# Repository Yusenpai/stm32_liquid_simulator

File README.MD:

# Giả lập chất lỏng trên STM32U585

Đây là một mạch in nhỏ do mình thiết kế với vi điều khiển STM32U585CIU6, chạy giả lập chất lỏng, hiển thị chất lỏng lên màn hình LED đơn; có thể tương tác với người dùng bằng cách nghiêng, lắc. Ý tưởng dựa trên project của mixela (YT: [Fluid Simulation Pedant](https://www.youtube.com/watch?v=jis1MC5Tm8k&t=2007s))

## Cài đặt

Sử dụng STM32CubeIDE import project dưới dạng CMake, hoặc sử dụng VSCode kết hợp STM32 VSCode Extension và Cmake Tools. Build với cấu hình Release. File elf sau khi build nằm ở build/Release/.

## Phần mềm

### Hiển thị

Màn hình gồm 216 LED, tạo thành từ ma trận LED 16x16, với 4 góc bị khuyết để tạo thành hình tròn. LED được điều khiển trực tiếp bằng chân GPIO của vi điều khiển. Ma trận LED được nối với kỹ thuật Charlieplexing:

Ưu điểm:

- Số lượng chân GPIO dùng để điều khiển màn hình LED là tối thiểu
- Tận dụng tốc độ bật tắt cao của chân GPIO vi điều khiển, tối đa 80MHz (nguồn :datasheet). Không cần dùng IC ngoài.
- Đơn giản hoá vẽ mạch in: Số lượng via sử dụng ít, cho phép đặt linh kiện ngay dưới màn hình LED. Bạn có thể xem phần giải thích ở video của mixela ().
- Độ sáng đồng nhất, do tại một thời điểm chỉ có một LED sáng.

Nhược điểm:

- Khó hiểu, khó sử dụng: ứng dụng tính chất 3 trạng thái của chân GPIO để điều khiển LED, dẫn đến khó sử dụng hơn những phương pháp điều khiển LED khác.
- Phần mềm phức tạp: Cần phải điều khiển GPIO với tốc độ rất cao, tiêu tốn nhiều tài nguyên CPU. Tại một thời điểm chỉ điều khiển được 1 LED sáng/tắt nên tốc độ quét trên LED phải rất cao.

### Điều khiển màn hình LED với STM32U585

- Có tất cả 216 LED. Do giới hạn của charlieplexing nên chỉ điều khiển sáng/tắt được 1 LED theo ý muốn. Trong một khoảng thời gian nhỏ (1ms), chia thành 216 phần thời gian bằng nhau, mỗi phần thời gian dành cho 1 LED. Do mắt lưu ảnh (nguồn -) nên mắt sẽ nhìn thấy toàn bộ bức ảnh do 216 LED tạo thành. Một khung ảnh (tạo thành từ 216 LED) cần 1ms để hiển thị. Vậy tốc độ làm mới (FPS) là 1000Hz.
- Điều khiển 1 LED sáng tắt bằng cách ghi vào hai thanh ghi ODR và MODER của GPIOA. ODR điều khiển mức điện áp (0/1). MODER điều khiển chế độ là ngõ ra hay ngõ vào (trở kháng cao).
- Mỗi LED sáng tương ứng với một giá trị của ODR và một giá trị MODER. Tất cả giá trị này được tính sẵn cho 216 LED và lưu vào một mảng. Khi cần sáng LED nào thì lấy giá trị tương ứng từ mảng này, lưu vào một mảng tạm. Led không sáng thì ODR = 0 và MODER = 0.
- Mảng tạm chứa tất cả các LED cần sáng để tạo thành ảnh. GPDMA thay thế cho CPU di chuyển dữ liệu từ mảng này sang hai thanh ghi GPIOA->ODR và GPIOA->MODER với tốc độ cao. Với mỗi LED GPDMA sử dụng hai kênh, một kênh để ghi vào ODR, một kênh ghi vào MODER. Hai kênh tuy độc lập lẫn nhau, như đều được trigger bởi một TIMER. Khi trigger xảy ra, cả hai thanh ghi ODR và MODER gần như được ghi cùng lúc, giúp giảm hiện tượng nhiễu màn hình. Kết hợp với chế độ circular mode và 2D addressing, GPDMA tự động chuyển sang LED tiếp theo cần sáng rồi chờ trigger từ timer; khi tới phần tử cuối trong mảng tạm, GPDMA tự động quay vòng địa chỉ về phần tử đầu tiên.
- TIMER15 được cấu hình đếm lên và reset mỗi 1/216 ms. Tín hiệu trigger gửi tới GPDMA điều khiển hoạt động của nó.
  
### Mô phỏng chất lỏng

- CPU của STM32U585 dành 100% thời gian để chạy mô phỏng chất lỏng. Phần mềm mô phỏng chất lỏng sử dụng phương pháp FLIP (Fluid Implicit Particle). Tham khảo tại [đây](https://www.sciencedirect.com/science/article/abs/pii/0010465588900203)
- Phần mềm được port sang C để tương thích với vi điều khiển. Phần mềm chưa hoàn toàn tối ưu. Nếu bạn muốn tự viết một cái, tham khảo kênh YT [Ten Minute Physics](https://www.youtube.com/@TenMinutePhysics/videos).
- MPU6050 là cảm biến dùng để đo hướng và độ lớn của gia tốc trọng trường. Giá trị này được truyền vào hàm mô phỏng chất lỏng. Giao tiếp I2C với MPU6050 ở chế độ non-block sử dụng DMA hoặc ngắt.
- CPU chạy ở tần số 160MHz. CPU chạy hàm mô phỏng mỗi 1/60 cho tốc độ cập nhật khung hình là 60 FPS.

### Chế độ tiết kiệm điện

- Khi không tương tác với người dùng (để yên một chỗ) lâu hơn 5s, vi điều khiển sẽ đi ngủ. Khi lắc mạnh sẽ tỉnh dậy. MPU6050 có lõi xử lý bên trong có khả năng gọi MCU tỉnh dậy khi phát hiện gia tốc lớn. Cái này là ý tưởng thôi chứ mình lười nên chưa làm.
- Mạch xài pin LIR2450 là loại pin đồng xu sạc lại được. Tuy nhiên nó có dung lượng nhỏ (khoảng 50mAh). Sử dụng liên tục trong khoảng 1h là hết pin.

## Phần cứng

- Mạch in hình tròn bán kính 1.5cm. Vừa đủ lớn để nhét vừa màn hình 16x16 LED (mỗi LED 0402).
- Do màn hình LED phải dùng rất nhiều Via nên đặt linh kiện ở mặt sau rất khó. May là charlieplexing có biến thể sử dụng ít via hơn, vừa đủ chỗ đặt con vi xử lý và mấy linh kiện bé.
- Mạch in 6 lớp. Dùng mạch in 4 lớp vẫn dư chỗ. Nhưng bên JLCPCB đang giảm giá với mình muốn cái mạch được mạ vàng nên dùng 6 lớp.
- Vi điều khiển STM32U585CIU6. Con này khá là mới (ra năm 2021). Mình dùng nó vì mình có sẵn. Nếu bạn muốn tự mình thiết kế lại, có thể thay con này bằng con nhỏ hơn, với điều kiện:
  - Có FPU. Giả lập chất lỏng làm toán chấm động là chính.
  - Có ít nhất 2 kênh DMA.
  - Điều khiển màn LED cần 16 chân GPIO. Chung 1 port càng tốt, vì chỉ cần điều khiển 2 thanh ghi của port đó để điều khiển cái màn hình LED (ODR và MODER). Nếu làm 2 port thì phải dùng 4 kênh DMA để điều khiển.
  - Tần số hoạt động > 100MHz. Cái này mình đoán dựa trên video của mixela và phần cứng của mình. CPU phải đủ mạnh mới mô phỏng được ở 60FPS. Không thì bạn có thể giảm FPS xuống và chấp nhận dùng chip yếu hơn.
  - Số chân GPIO: đủ cho 16 chân điều khiển màn hình, không nên quá nhiều chân vì nó sẽ to và không đặt lên mạch được.
- Vỏ: mình có vẽ một cái vỏ nữa, nhưng nó khá là xấu.

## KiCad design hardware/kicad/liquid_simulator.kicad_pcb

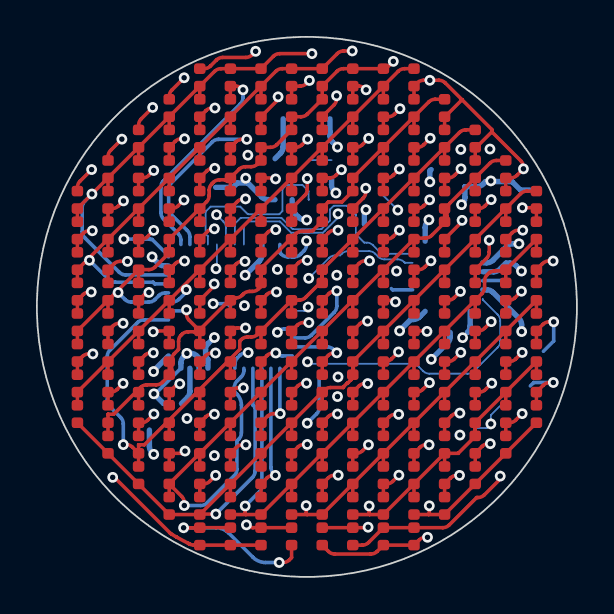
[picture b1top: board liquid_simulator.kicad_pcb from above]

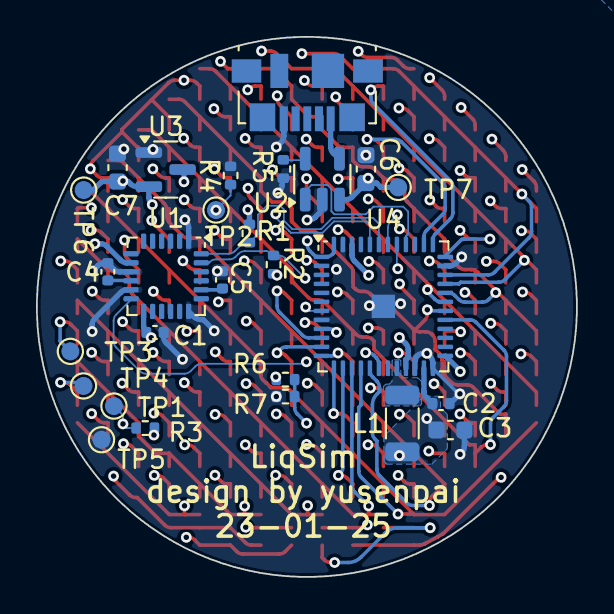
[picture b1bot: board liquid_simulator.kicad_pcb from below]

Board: 6 copper layers, 30.0 x 30.0 mm, 243 parts (27 on the bottom side), 32 nets.

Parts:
C1, C4: 100n; C_0402_1005Metric
C2: 470n; C_0402_1005Metric
C3: 4u7; C_0603_1608Metric
C5: 2n2.50V; C_0402_1005Metric
C6, C7: 1u; C_0603_1608Metric
D1, D2, D3, D4, D5, D6, D7, D8, D9, D10, D11, D12, D13, D14, D15, D16, D17, D18, D19, D20, D21, D22, D23, D24, D25, D26, D27, D28, D29, D30, D31, D32, D33, D34, D35, D36, D37, D38, D39, D40, D41, D42, D43, D44, D45, D46, D47, D48, D49, D50, D51, D52, D53, D54, D55, D56, D57, D58, D59, D60, D61, D62, D63, D64, D65, D66, D67, D68, D69, D70, D71, D72, D73, D74, D75, D76, D77, D78, D79, D80, D81, D82, D83, D84, D85, D86, D87, D88, D89, D90, D91, D92, D93, D94, D95, D96, D97, D98, D99, D100, D101, D102, D103, D104, D105, D106, D107, D108, D109, D110, D111, D112, D113, D114, D115, D116, D117, D118, D119, D120, D121, D122, D123, D124, D125, D126, D127, D128, D129, D130, D131, D132, D133, D134, D135, D136, D137, D138, D139, D140, D141, D142, D143, D144, D145, D146, D147, D148, D149, D150, D151, D152, D153, D154, D155, D156, D157, D158, D159, D160, D161, D162, D163, D164, D165, D166, D167, D168, D169, D170, D171, D172, D173, D174, D175, D176, D177, D178, D179, D180, D181, D182, D183, D184, D185, D186, D187, D188, D189, D190, D191, D192, D193, D194, D195, D196, D197, D198, D199, D200, D201, D202, D203, D204, D205, D206, D207, D208, D209, D210, D211, D212, D213, D214, D215, D216: LED_Small; LED_0402_1005Metric_No_Ink
J1: USB_B_Micro; USB_Micro-B_Molex_47346-0001
L1: 2u2; L_1206_3216Metric
R1, R2, R3, R4: 10k; R_0402_1005Metric
R5: 33k; R_0402_1005Metric
R6, R7: 100k; R_0402_1005Metric
TP1: NRST; TestPoint_Pad_D1.0mm
TP2: BOOT0; TestPoint_Pad_D1.0mm
TP3: SWDIO; TestPoint_Pad_D1.0mm
TP4: SWCLK; TestPoint_Pad_D1.0mm
TP5: GND; TestPoint_Pad_D1.0mm
TP6: +3V3; TestPoint_Pad_D1.0mm
TP7: VBAT; TestPoint_Pad_D1.0mm
U1: MPU-6050; InvenSense_QFN-24_4x4mm_P0.5mm
U2: SOT-23-5
U3: MCP1700x-330xxTT; SOT-23
U4: STM32U585CIUxQ; QFN-48-1EP_7x7mm_P0.5mm_Small_EP

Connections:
+BATT: C6.1, R6.1, TP7.1, U2.3 (BAT), U3.3 (VI)
/BATT_ADC: R6.2, R7.2, U4.18 (PB0)
/BOOT0: R4.1, TP2.1, U4.44 (PH3)
/CHRG_INT: U2.1 (CHRG), U4.40 (PB4)
/D1: D19.1 (K), D20.2 (A), D33.1 (K), D34.2 (A), D49.1 (K), D50.2 (A), D66.1 (K), D67.2 (A), D83.1 (K), D84.2 (A), D100.1 (K), D101.2 (A), D117.1 (K), D118.2 (A), D134.1 (K), D135.2 (A), D151.1 (K), D152.2 (A), D168.1 (K), D169.2 (A), D184.1 (K), D185.2 (A), D198.1 (K), D214.2 (A), D215.2 (A), D216.1 (K), U4.10 (PA0)
/D2: D9.1 (K), D10.2 (A), D21.1 (K), D22.2 (A), D35.1 (K), D36.2 (A), D51.1 (K), D52.2 (A), D68.1 (K), D69.2 (A), D85.1 (K), D86.2 (A), D102.1 (K), D103.2 (A), D119.1 (K), D120.2 (A), D136.1 (K), D137.2 (A), D153.1 (K), D154.2 (A), D170.1 (K), D171.2 (A), D186.1 (K), U4.38 (PA15)
/D3: D31.1 (K), D32.2 (A), D47.1 (K), D48.2 (A), D64.1 (K), D65.2 (A), D81.1 (K), D82.2 (A), D98.1 (K), D99.2 (A), D115.1 (K), D116.2 (A), D132.1 (K), D133.2 (A), D149.1 (K), D150.2 (A), D166.1 (K), D167.2 (A), D182.1 (K), D183.2 (A), D196.1 (K), D197.2 (A), D208.1 (K), D213.2 (A), D215.1 (K), D216.2 (A), U4.11 (PA1)
/D4: D1.1 (K), D2.2 (A), D11.1 (K), D12.2 (A), D23.1 (K), D24.2 (A), D37.1 (K), D38.2 (A), D53.1 (K), D54.2 (A), D70.1 (K), D71.2 (A), D87.1 (K), D88.2 (A), D104.1 (K), D105.2 (A), D121.1 (K), D122.2 (A), D138.1 (K), D139.2 (A), D155.1 (K), D156.2 (A), D172.2 (A), TP4.1, U4.37 (PA14)
/D5: D45.1 (K), D46.2 (A), D62.1 (K), D63.2 (A), D79.1 (K), D80.2 (A), D96.1 (K), D97.2 (A), D113.1 (K), D114.2 (A), D130.1 (K), D131.2 (A), D147.1 (K), D148.2 (A), D164.1 (K), D165.2 (A), D172.1 (K), D180.1 (K), D181.2 (A), D186.2 (A), D194.1 (K), D195.2 (A), D198.2 (A), D206.1 (K), D207.2 (A), D208.2 (A), D213.1 (K), D214.1 (K), U4.12 (PA2)
/D6: D1.2 (A), D2.1 (K), D3.1 (K), D4.2 (A), D9.2 (A), D10.1 (K), D13.1 (K), D14.2 (A), D19.2 (A), D20.1 (K), D25.1 (K), D26.2 (A), D31.2 (A), D32.1 (K), D39.1 (K), D40.2 (A), D45.2 (A), D46.1 (K), D55.1 (K), D56.2 (A), D61.1 (K), D72.1 (K), D73.2 (A), D89.1 (K), D90.2 (A), D106.1 (K), D107.2 (A), D123.1 (K), D124.2 (A), D140.2 (A), TP3.1, U4.34 (PA13)
/D7: D61.2 (A), D77.1 (K), D78.2 (A), D94.1 (K), D95.2 (A), D111.1 (K), D112.2 (A), D128.1 (K), D129.2 (A), D140.1 (K), D145.1 (K), D146.2 (A), D155.2 (A), D156.1 (K), D162.1 (K), D163.2 (A), D170.2 (A), D171.1 (K), D178.1 (K), D179.2 (A), D184.2 (A), D185.1 (K), D192.1 (K), D193.2 (A), D196.2 (A), D197.1 (K), D204.1 (K), D205.2 (A), D206.2 (A), D207.1 (K), U4.13 (PA3)
/D8: D3.2 (A), D4.1 (K), D5.1 (K), D6.2 (A), D11.2 (A), D12.1 (K), D15.1 (K), D16.2 (A), D21.2 (A), D22.1 (K), D27.1 (K), D28.2 (A), D33.2 (A), D34.1 (K), D41.1 (K), D42.2 (A), D47.2 (A), D48.1 (K), D57.1 (K), D58.2 (A), D62.2 (A), D63.1 (K), D74.1 (K), D75.2 (A), D77.2 (A), D78.1 (K), D91.1 (K), D92.2 (A), D93.1 (K), D108.2 (A), U4.33 (PA12)
/D9: D93.2 (A), D108.1 (K), D109.1 (K), D110.2 (A), D123.2 (A), D124.1 (K), D126.1 (K), D127.2 (A), D138.2 (A), D139.1 (K), D143.1 (K), D144.2 (A), D153.2 (A), D154.1 (K), D160.1 (K), D161.2 (A), D168.2 (A), D169.1 (K), D176.1 (K), D177.2 (A), D182.2 (A), D183.1 (K), D190.1 (K), D191.2 (A), D194.2 (A), D195.1 (K), D202.1 (K), D203.2 (A), D204.2 (A), D205.1 (K), U4.14 (PA4)
/D10: D5.2 (A), D6.1 (K), D7.1 (K), D8.2 (A), D13.2 (A), D14.1 (K), D17.1 (K), D18.2 (A), D23.2 (A), D24.1 (K), D29.1 (K), D30.2 (A), D35.2 (A), D36.1 (K), D43.1 (K), D44.2 (A), D49.2 (A), D50.1 (K), D59.1 (K), D60.2 (A), D64.2 (A), D65.1 (K), D76.1 (K), D79.2 (A), D80.1 (K), D94.2 (A), D95.1 (K), D109.2 (A), D110.1 (K), D125.1 (K), U4.32 (PA11)
/D11: D76.2 (A), D91.2 (A), D92.1 (K), D106.2 (A), D107.1 (K), D121.2 (A), D122.1 (K), D125.2 (A), D136.2 (A), D137.1 (K), D141.1 (K), D142.2 (A), D151.2 (A), D152.1 (K), D158.1 (K), D159.2 (A), D166.2 (A), D167.1 (K), D174.1 (K), D175.2 (A), D180.2 (A), D181.1 (K), D188.1 (K), D189.2 (A), D192.2 (A), D193.1 (K), D200.1 (K), D201.2 (A), D202.2 (A), D203.1 (K), U4.15 (PA5)
/D12: D7.2 (A), D8.1 (K), D15.2 (A), D16.1 (K), D25.2 (A), D26.1 (K), D37.2 (A), D38.1 (K), D51.2 (A), D52.1 (K), D66.2 (A), D67.1 (K), D81.2 (A), D82.1 (K), D96.2 (A), D97.1 (K), D111.2 (A), D112.1 (K), D126.2 (A), D127.1 (K), D141.2 (A), D142.1 (K), D157.1 (K), U4.31 (PA10)
/D13: D59.2 (A), D60.1 (K), D74.2 (A), D75.1 (K), D89.2 (A), D90.1 (K), D104.2 (A), D105.1 (K), D119.2 (A), D120.1 (K), D134.2 (A), D135.1 (K), D149.2 (A), D150.1 (K), D157.2 (A), D164.2 (A), D165.1 (K), D173.2 (A), D178.2 (A), D179.1 (K), D187.2 (A), D190.2 (A), D191.1 (K), D199.2 (A), D200.2 (A), D201.1 (K), D211.1 (K), D212.1 (K), U4.16 (PA6)
/D14: D17.2 (A), D18.1 (K), D27.2 (A), D28.1 (K), D39.2 (A), D40.1 (K), D53.2 (A), D54.1 (K), D68.2 (A), D69.1 (K), D83.2 (A), D84.1 (K), D98.2 (A), D99.1 (K), D113.2 (A), D114.1 (K), D128.2 (A), D129.1 (K), D143.2 (A), D144.1 (K), D158.2 (A), D159.1 (K), D173.1 (K), U4.30 (PA9)
/D15: D43.2 (A), D44.1 (K), D57.2 (A), D58.1 (K), D72.2 (A), D73.1 (K), D87.2 (A), D88.1 (K), D102.2 (A), D103.1 (K), D117.2 (A), D118.1 (K), D132.2 (A), D133.1 (K), D147.2 (A), D148.1 (K), D162.2 (A), D163.1 (K), D176.2 (A), D177.1 (K), D188.2 (A), D189.1 (K), D199.1 (K), D209.1 (K), D210.2 (A), D212.2 (A), U4.17 (PA7)
/D16: D29.2 (A), D30.1 (K), D41.2 (A), D42.1 (K), D55.2 (A), D56.1 (K), D70.2 (A), D71.1 (K), D85.2 (A), D86.1 (K), D100.2 (A), D101.1 (K), D115.2 (A), D116.1 (K), D130.2 (A), D131.1 (K), D145.2 (A), D146.1 (K), D160.2 (A), D161.1 (K), D174.2 (A), D175.1 (K), D187.1 (K), D209.2 (A), D210.1 (K), D211.2 (A), U4.29 (PA8)
/I2C_SCL: R2.2, U1.23 (SCL), U4.42 (PB6)
/I2C_SDA: R1.2, U1.24 (SDA), U4.43 (PB7)
/IMU_INT: U1.12 (INT), U4.41 (PB5)
/NRST: R3.2, TP1.1, U4.7 (NRST)
GND: C1.2, C2.2, C3.2, C4.2, C5.2, C6.2, C7.2, J1.5 (GND), R4.2, R5.1, R7.1, TP5.1, U1.1 (CLKIN), U1.9 (AD0), U1.11 (FSYNC), U1.18 (GND), U2.2 (GND), U3.1 (GND), U4.8 (VSSA), U4.22 (VSSSMPS), U4.24 (VSS), U4.35 (VSS), U4.47 (VSS), U4.49 (VSS)
unnamed: C5.1, U1.20 (CPOUT)
unnamed: C4.1, U1.10 (REGOUT)
unnamed: R5.2, U2.5 (PROG)
unnamed: L1.2, U4.20 (VLXSMPS)
VCC: J1.1 (VBUS), U2.4 (VCC)
VDD: C1.1, C7.1, R1.1, R2.1, R3.1, TP6.1, U1.8 (VLOGIC), U1.13 (VDD), U3.2 (VO), U4.1 (VBAT), U4.9 (VDDA), U4.21 (VDDSMPS), U4.25 (VDD), U4.36 (VDD), U4.48 (VDD)
VDD11: C2.1, C3.1, L1.1, U4.23 (VDD11), U4.46 (VDD11)

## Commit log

2025-04-02 remove build
2025-04-04 Create LICENSE
2025-04-04 sửa lại cấu trúc folder
2025-04-04 remove some unused file
2025-04-04 add demo
